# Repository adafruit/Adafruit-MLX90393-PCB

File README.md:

## Adafruit Wide-Range Triple-axis Magnetometer - MLX90393 PCB

<a href="http://www.adafruit.com/products/4022"><br/>
<a href="http://www.adafruit.com/products/4022"><br/>
Click here to purchase one from the Adafruit shop</a>

PCB files for the Adafruit Wide-Range Triple-axis Magnetometer - MLX90393. Format is EagleCAD schematic and board layout
* https://www.adafruit.com/product/4022

### Description

Measure the invisible magnetic fields that surround us, with this wide-range magnetometer. The MLX90393 is a wide range magnetic field sensor, that can measure 16-bits in ranges from ±5mT up to ±50mT in all 3 axes.

Compared to most magnetometers, this gives a huge range, which makes it excellent for detecting magnets and magnetic orientation, rather than the Earth's magnetic field. (Magnets have a much stronger field that overwhelms most magnetometers that would normally be used for orientation with respect to the North Pole)

To make it easy to use, we've placed this tiny little sensor onto a breakout board, with a 3.3V power supply and level shifter. This makes it easy to use with any 3 or 5V microcontroller. Our Arduino and CircuitPython code will get you started in a jiffy, with I2C communication to the sensor. You will be readin' out those Gauss's in minutes! With the address select pins you can have up to 4 sensors on one I2C bus.

Comes as a fully assembled and tested breakout board with a small piece of header for use with a breadboard. As if that weren't enough, we've now also added SparkFun qwiic compatible STEMMA QT connectors for the I2C bus so you don't even need to solder the I2C and power lines. Just wire up to your favorite micro using a STEMMA QT adapter cable. The Stemma QT connectors also mean the MLX90393 can be used with our various associated accessories. QT Cable is not included, but we have a variety in the shop.

**Specifications**
The MLX90393 has the following key technical specifications:

 * 16-bit output on all three (XYZ) magnetic field sensors
 * An unusually large dynamic range of **5-50** mT (1 mT or millitesla = 10 G or Gauss).
 * By comparison, the LSM303DLHC saturates at +/-8.1 G (0.81 mT) at maximum range setting.
 * Up to ~500 Hz sample rate (Based on OSR=0, DIG_FILT=2, HALLCONF=0xC for **1.84ms** conversion time. See 15.1.5 HALLCONF [3:0] in the datasheet for details.)
 * User-adjustable I2C address to allow multiple sensors in your project (two I2C ADDR pins for four possible I2C addresses).

### License

Adafruit invests time and resources providing this open source design, please support Adafruit and open-source hardware by purchasing products from [Adafruit](https://www.adafruit.com)!

Designed by Limor Fried/Ladyada for Adafruit Industries.

Creative Commons Attribution/Share-Alike, all text above must be included in any redistribution. See license.txt for additional details.

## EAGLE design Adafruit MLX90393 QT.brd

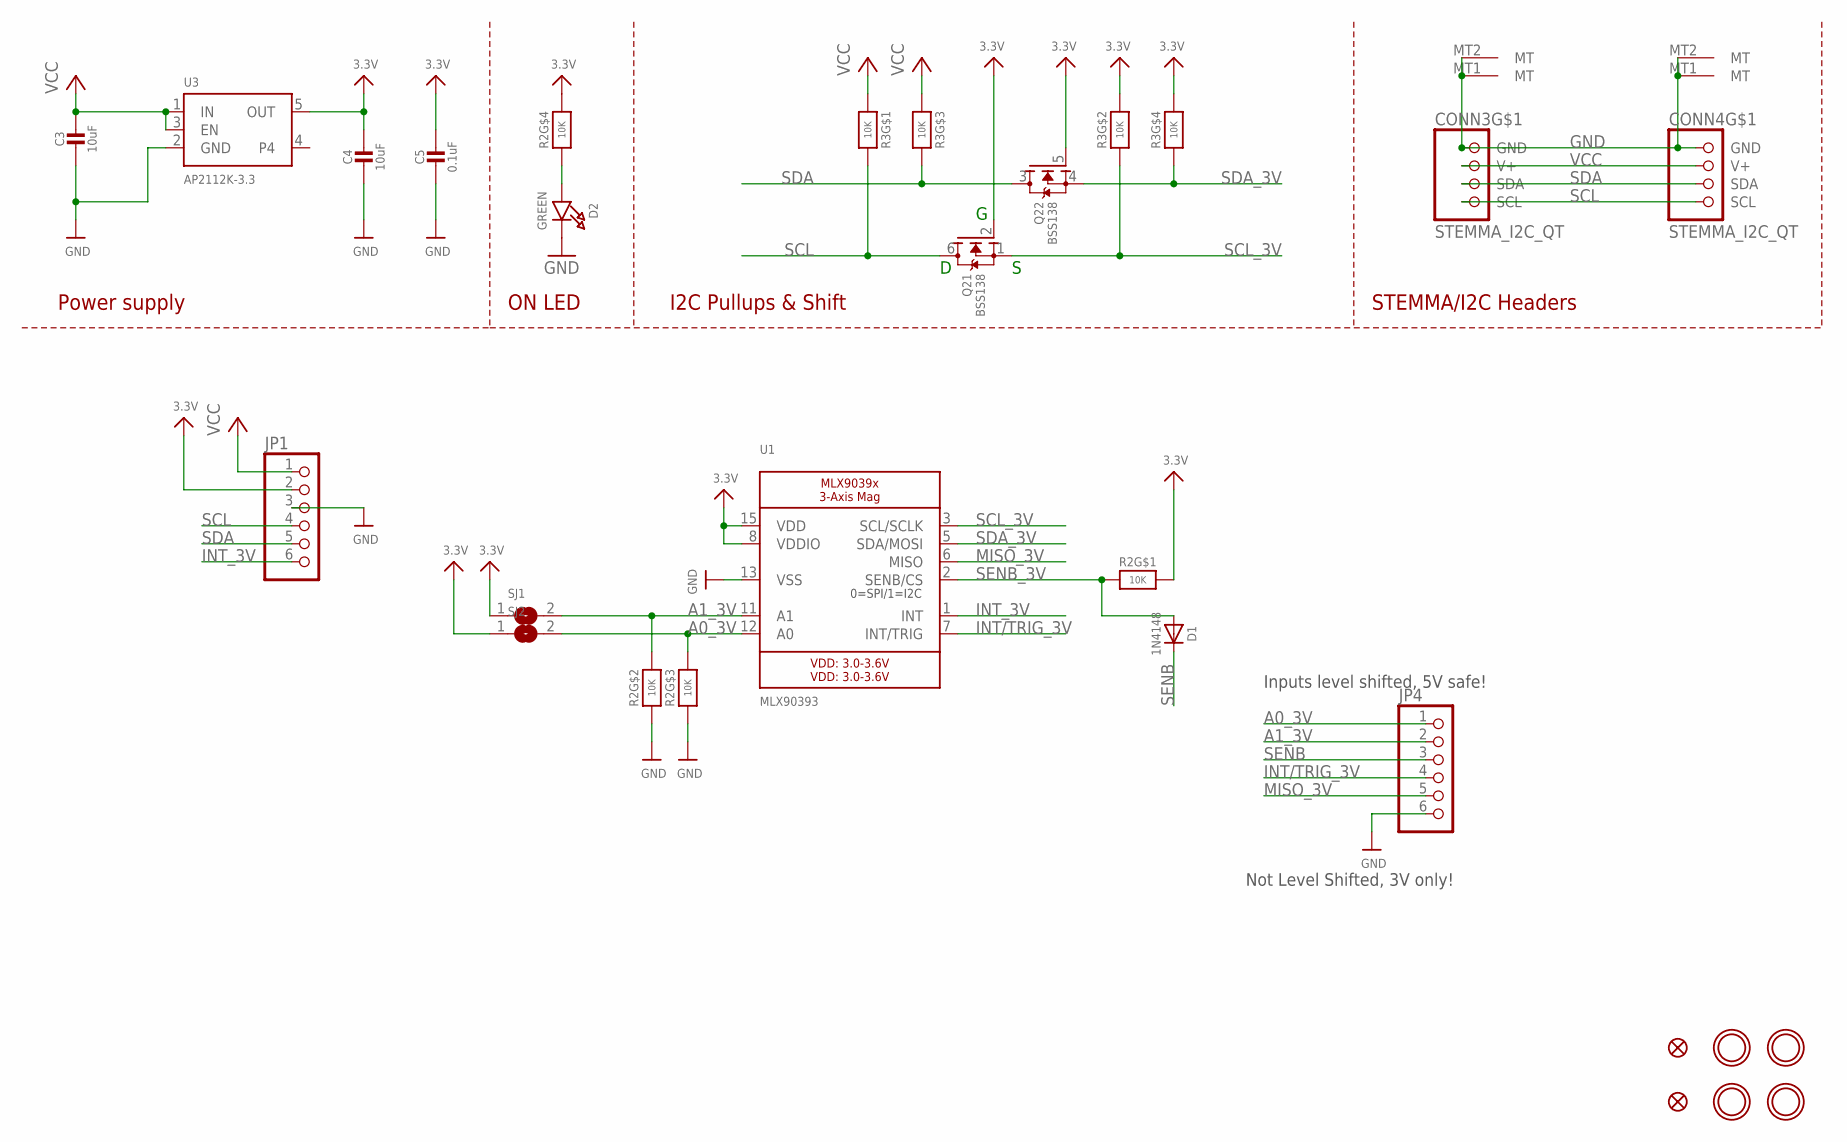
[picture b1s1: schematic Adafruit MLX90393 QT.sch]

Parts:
C3, C4: 10uF; 0805-NO
C5: 0.1uF; 0603-NO
CONN3, CONN4: STEMMA_I2C_QT; JST_SH4
D1: 1N4148; SOD-323_MINI
D2: GREEN; CHIPLED_0603_NOOUTLINE
FID2, FID4: FIDUCIAL_1MM
JP1, JP4: HEADER-1X670MIL; 1X06_ROUND_70
Q2: BSS138; SOT363
R2: 10K; RESPACK_4X0603_NO
R3: 10K; RESPACK_4X0603
SJ1, SJ2: SOLDERJUMPER; SOLDERJUMPER_ARROW_NOPASTE
U1: MLX90393; QFN16_3MM
U3: AP2112K-3.3; SOT23-5
U$33, U$34, U$36, U$37: MOUNTINGHOLE2.5; MOUNTINGHOLE_2.5_PLATED

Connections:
3.3V: C4.1, C5.1, JP1.2, Q2.2 (G), Q2.5 (G), R2.5 (2), R2.8 (2), R3.2 (1), R3.4 (1), SJ1.1, SJ2.1, U1.8 (VDDIO), U1.15 (VDD), U3.5 (OUT)
A0_3V: JP4.1, R2.6 (2), SJ2.2, U1.12 (A0)
A1_3V: JP4.2, R2.7 (2), SJ1.2, U1.11 (A1)
GND: C3.2, C4.2, C5.2, CONN3.1 (GND), CONN3.MT1 (MT), CONN3.MT2 (MT), CONN4.1 (GND), CONN4.MT1 (MT), CONN4.MT2 (MT), D2.C, JP1.3, JP4.6, R2.2 (1), R2.3 (1), U1.13 (VSS), U3.2 (GND)
INT/TRIG_3V: JP4.4, U1.7 (INT/TRIG)
INT_3V: JP1.6, U1.1 (INT)
MISO_3V: JP4.5, U1.6 (MISO)
unnamed: D2.A, R2.4 (1)
SCL: CONN3.4 (SCL), CONN4.4 (SCL), JP1.4, Q2.6 (D), R3.8 (2)
SCL_3V: Q2.1 (S), R3.7 (2), U1.3 (SCL/SCLK)
SDA: CONN3.3 (SDA), CONN4.3 (SDA), JP1.5, Q2.3 (D), R3.6 (2)
SDA_3V: Q2.4 (S), R3.5 (2), U1.5 (SDA/MOSI)
SENB: D1.C, JP4.3
SENB_3V: D1.A, R2.1, U1.2 (SENB/CS)
VCC: C3.1, CONN3.2 (V+), CONN4.2 (V+), JP1.1, R3.1, R3.3 (1), U3.1 (IN), U3.3 (EN)

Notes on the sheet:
I2C Pullups & Shift
STEMMA/I2C Headers
ON LED
Power supply
Not Level Shifted, 3V only!
Inputs level shifted, 5V safe!

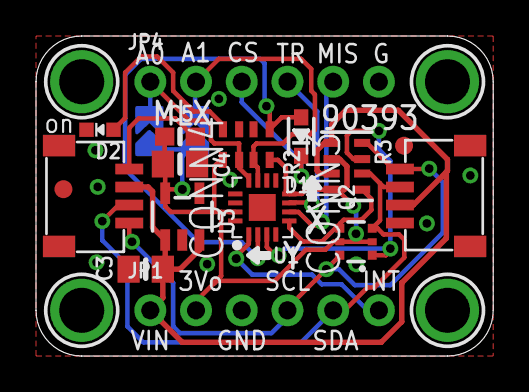
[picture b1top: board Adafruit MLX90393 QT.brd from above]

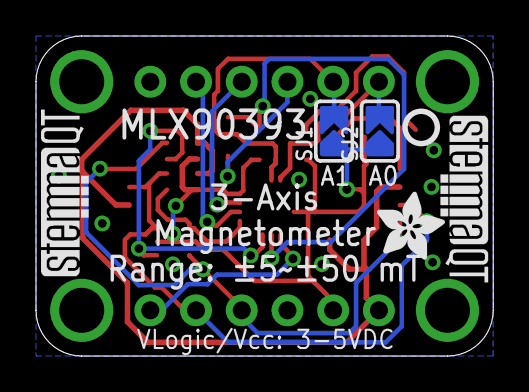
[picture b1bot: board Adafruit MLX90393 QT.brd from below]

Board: 2 copper layers, 25.4 x 17.8 mm, 26 parts (6 on the bottom side), 15 nets.

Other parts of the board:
U$18: PCBFEAT-REV-040
U$39: ADAFRUIT_3.5MM
U$41, U$42: STEMMAQT

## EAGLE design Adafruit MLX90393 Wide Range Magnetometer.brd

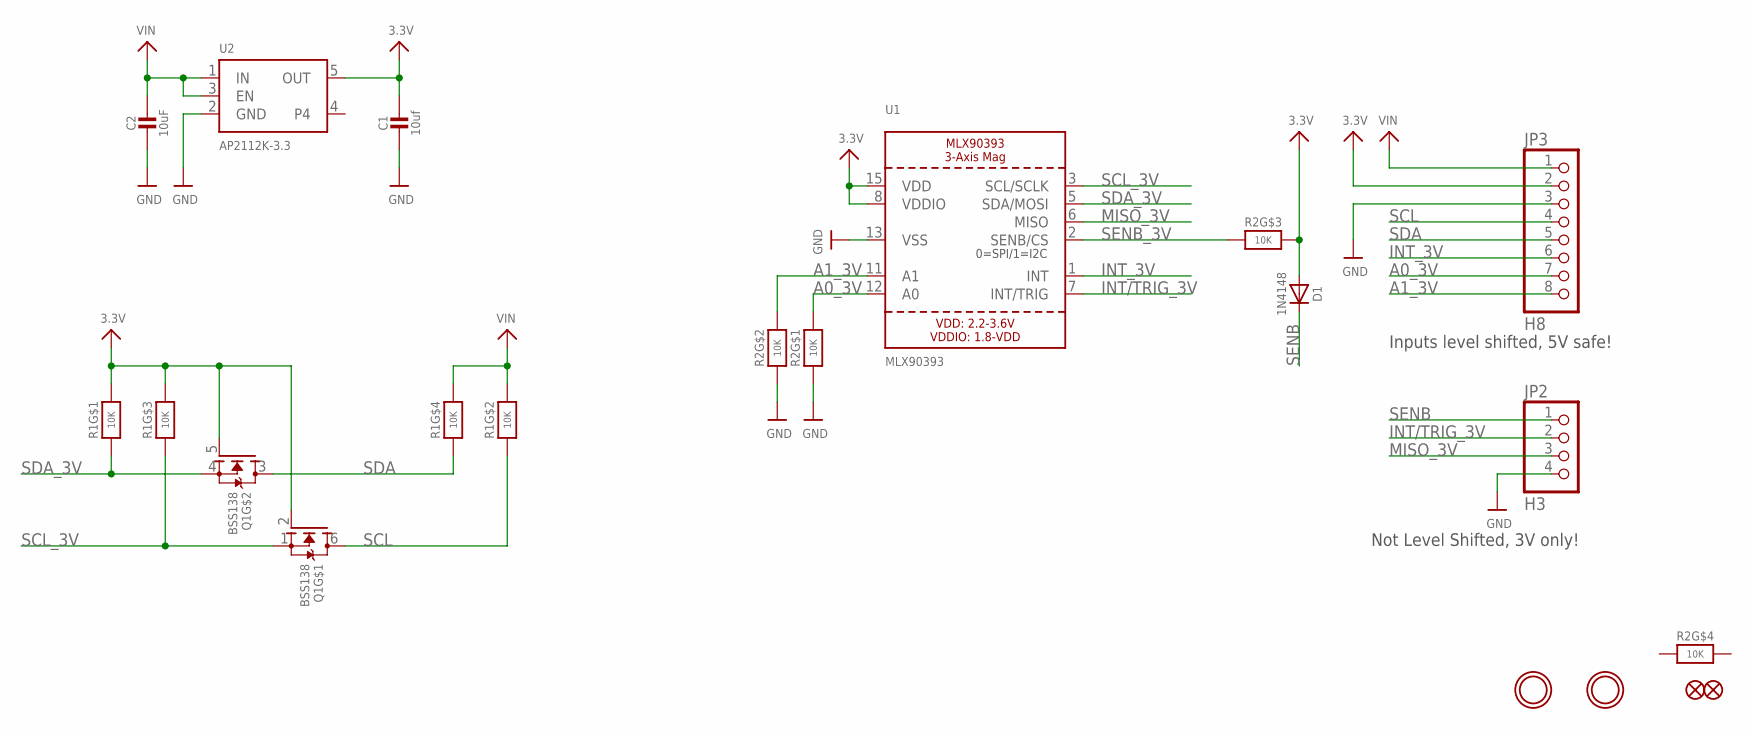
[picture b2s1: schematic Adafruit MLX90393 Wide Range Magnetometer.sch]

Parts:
C1: 10uf; 0805_10MGAP
C2: 10uF; 0805_10MGAP
D1: 1N4148; SOD-323
FID1, FID3: FIDUCIAL_1MM
JP2: H3; 1X04_ROUND
JP3: H8; 1X08_ROUND
Q1: BSS138; SOT363
R1, R2: 10K; RESPACK_4X0603_NO
U1: MLX90393; QFN16_3MM
U2: AP2112K-3.3; SOT23-5
U$19, U$23: MOUNTINGHOLE2.5; MOUNTINGHOLE_2.5_PLATED

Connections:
3.3V: C1.1, D1.A, JP3.2, Q1.2 (G), Q1.5 (G), R1.6 (2), R1.8 (2), R2.6 (2), U1.8 (VDDIO), U1.15 (VDD), U2.5 (OUT)
A0_3V: JP3.7, R2.8 (2), U1.12 (A0)
A1_3V: JP3.8, R2.7 (2), U1.11 (A1)
GND: C1.2, C2.2, JP2.4, JP3.3, R2.1, R2.2 (1), U1.13 (VSS), U2.2 (GND)
INT/TRIG_3V: JP2.2, U1.7 (INT/TRIG)
INT_3V: JP3.6, U1.1 (INT)
MISO_3V: JP2.3, U1.6 (MISO)
SCL: JP3.4, Q1.6 (D), R1.2 (1)
SCL_3V: Q1.1 (S), R1.3 (1), U1.3 (SCL/SCLK)
SDA: JP3.5, Q1.3 (D), R1.4 (1)
SDA_3V: Q1.4 (S), R1.1, U1.5 (SDA/MOSI)
SENB: D1.C, JP2.1
SENB_3V: R2.3 (1), U1.2 (SENB/CS)
VIN: C2.1, JP3.1, R1.5 (2), R1.7 (2), U2.1 (IN), U2.3 (EN)

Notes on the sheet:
Not Level Shifted, 3V only!
Inputs level shifted, 5V safe!

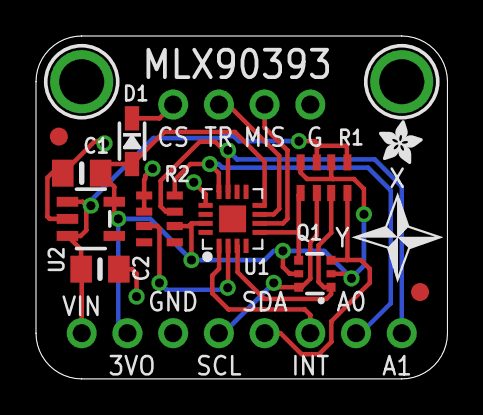
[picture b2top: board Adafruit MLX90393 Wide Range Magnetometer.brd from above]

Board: 2 copper layers, 22.9 x 19.1 mm, 17 parts (1 on the bottom side), 14 nets.

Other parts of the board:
U$3: SYMBOL_COMPASSXY_5MM
U$18: PCBFEAT-REV-040
U$21: ADAFRUIT_2.5MM

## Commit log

2019-02-13 Fix link
2019-02-13 Add PCB files.
2019-07-17 updated to use cookiecutter for pcb repos
2021-02-17 Add asset.
2021-02-17 Add board files.

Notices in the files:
parts and their libraries:
microbuilder: This work is placed in the public domain, and may be freely used for commercial and non-commercial work with the following conditions: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
